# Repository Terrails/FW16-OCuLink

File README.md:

# OCuLink 8i Expansion Board for the Framework 16

## The schematic

The schematic in itself is pretty simple. You only need to connect the TX and RX PCIe lanes to the correct pins of the OCuLink connector. And then add components such as the EEPROM that the Embedded Controller (EC) on the laptop reads to configure GPIO pins and bifurcation.

A pdf version of the schematic is available [here](./imgs/schematic.pdf).

### EEPROM
As for the EEPROM, I have decided to use the same one that Framework is using in their [Dual SSD reference design](https://github.com/FrameworkComputer/ExpansionBay/tree/main/Dual%20SSD%20Reference%20Design). The `BR24G32FVT-3GE2`. The chip is marked as not recommended for new design according to Mouser, but it still seems to be in stock, although it can easily be swapped with another if required.

The EEPROM's address pins are all connected to the ground as that is the address the EC expects and by default the write protection (WP) is disabled by being connected to GND to allow writing data to it.

### Fans
For the fans I had to go with an alternative FPC header, as the one Framework uses on their boards was not available anywhere. The connector I use is slightly smaller, but still makes the connection nevertheless and the fans do spin up. I have specifically went with the [`AFC05-S04FIA-00`](https://www.lcsc.com/product-detail/C561383.html) that is available on LCSC to use with JLCPCB's assembly.

## Firmware
The firmware file is generated using [Framework's Expansion Bay tool](https://github.com/FrameworkComputer/ExpansionBayConfigurationGenerator). More info on the specific file I have been using in my testing and how I flashed it *SOON*.

## The PCB layout

For the layout I have went with a 4-layer board and did manage to successfully stay within JLCPCB's fabrication limits. For the production runs I have done a 1.2mm ENIG board and used the `Nan Ya NP-140F` material type with the `JLC04121H-1080` stackup and matched the differential pairs to it. I did also manage to stay within the minimum 0.3mm via hole size to keep costs somewhat down.

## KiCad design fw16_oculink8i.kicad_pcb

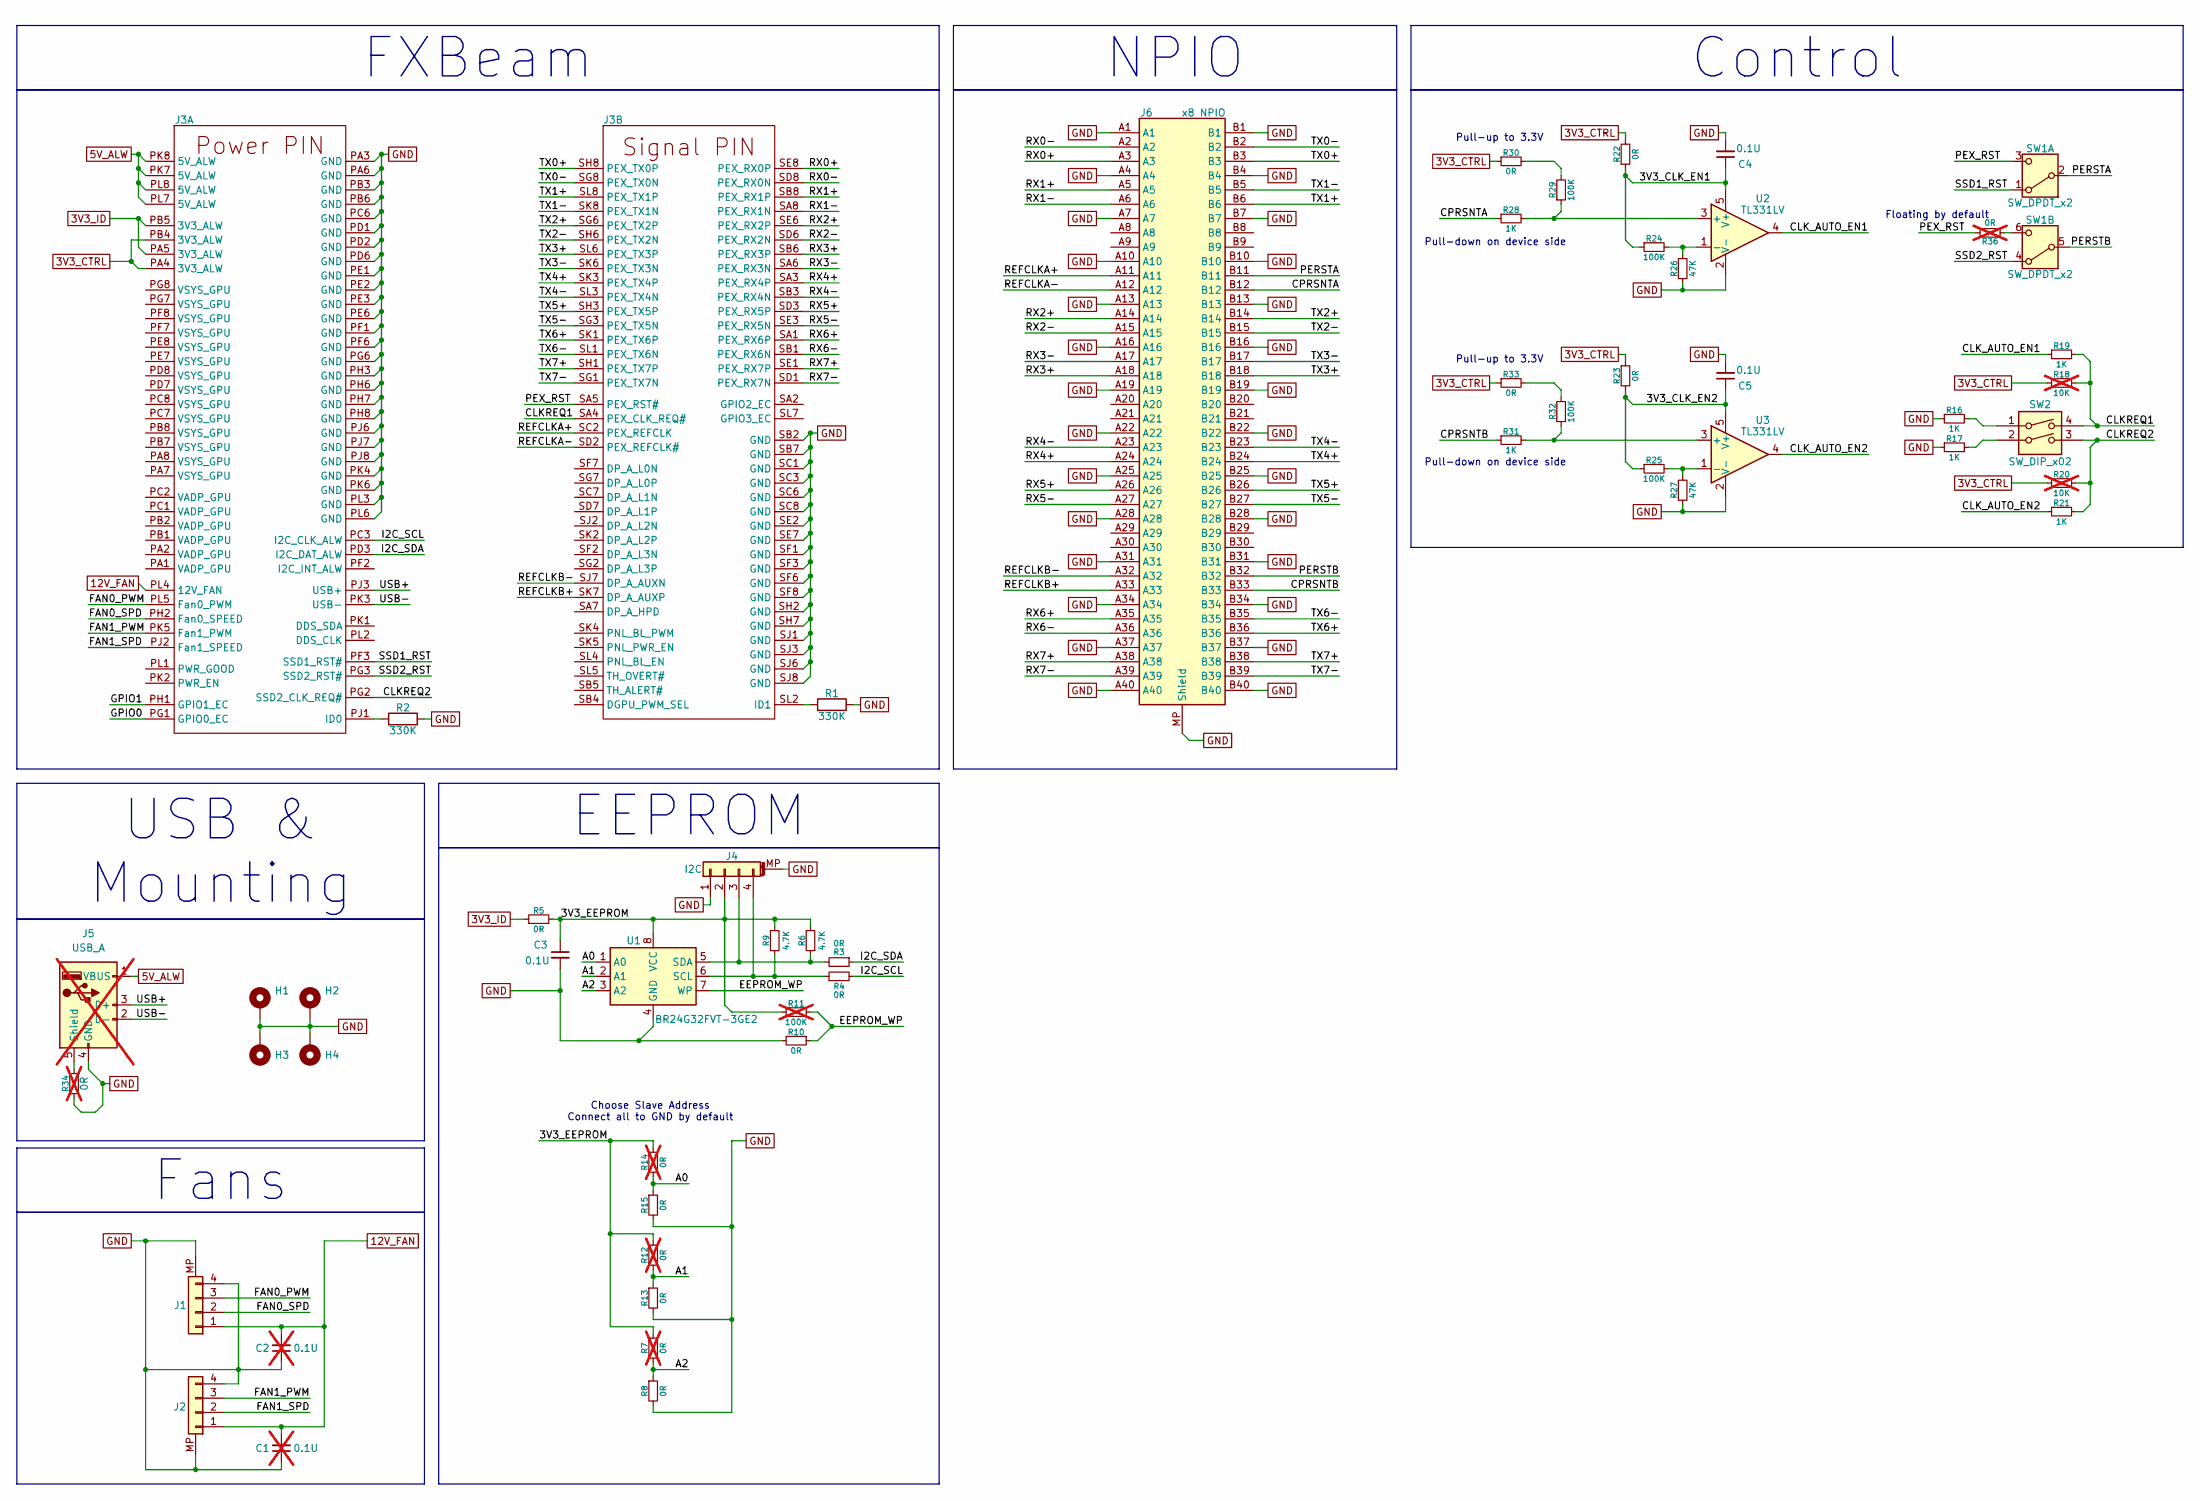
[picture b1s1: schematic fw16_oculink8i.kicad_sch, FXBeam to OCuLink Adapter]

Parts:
C1, C2: 0.1U; C_0402_1005Metric; not fitted
C3, C4, C5: 0.1U; C_0402_1005Metric
H1, H2, H3, H4: MountingHole_Pad; MountingHole_6.2mm_EasySolder_Cut
J1, J2: Fan; AFC58-S04FIA_4Pin; Part Nr. AFC58-S04FIA
J3: FXBeam
J4: I2C; JST_SH_SM04B-SRSS-TB_1x04-1MP_P1.00mm_Horizontal
J5: USB_A; 87583-2010BLF; not fitted
J6: x8 NPIO; Nano-Pitch-173162-0132
R1, R2: 330K; R_0402_1005Metric; Tolerance 1%
R3, R4, R5, R8, R10, R13, R15, R22, R23, R30, R33: 0R; R_0402_1005Metric
R6, R9: 4.7K; R_0402_1005Metric; Tolerance 1%
R7, R12, R14, R34, R36: 0R; R_0402_1005Metric; not fitted
R11: 100K; R_0402_1005Metric; Tolerance 1%; not fitted
R16, R17, R19, R21, R28, R31: 1K; R_0402_1005Metric
R18, R20: 10K; R_0402_1005Metric; not fitted
R24, R25, R29, R32: 100K; R_0402_1005Metric
R26, R27: 47K; R_0402_1005Metric
SW1: SW_DPDT_x2; SSSS820101
SW2: SW_DIP_x02; SW_DIP_SPSTx02_Slide_Copal_CHS-02B_W7.62mm_P1.27mm
U1: BR24G32FVT-3GE2; TSSOP-8_4.4x3mm_P0.65mm
U2, U3: TL331LV; SOT-23-5

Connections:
3V3_CTRL: J3.PA4 (3V3_ALW), J3.PB4 (3V3_ALW), R18.1, R20.1, R22.2, R23.1, R30.1, R33.1
3V3_ID: J3.PA5 (3V3_ALW), J3.PB5 (3V3_ALW), R5.1
5V_ALW: J3.PK7 (5V_ALW), J3.PK8 (5V_ALW), J3.PL7 (5V_ALW), J3.PL8 (5V_ALW), J5.1 (VBUS)
12V_FAN: C1.2, C2.2, J1.1, J2.1, J3.PL4 (12V_FAN)
/3V3_CLK_EN1: C4.1, R22.1, R24.1, U2.5 (V+)
/3V3_CLK_EN2: C5.1, R23.2, R25.1, U3.5 (V+)
/3V3_EEPROM: C3.1, J4.2, R5.2, R6.2, R7.1, R9.1, R11.2, R12.1, R14.1, U1.8 (VCC)
/A0: R14.2, R15.1, U1.1 (A0)
/A1: R12.2, R13.1, U1.2 (A1)
/A2: R7.2, R8.1, U1.3 (A2)
/CLKREQ1: J3.SA4 (PEX_CLK_REQ#), R18.2, R19.2, SW2.4
/CLKREQ2: J3.PG2 (SSD2_CLK_REQ#), R20.2, R21.2, SW2.3
/CLK_AUTO_EN1: R19.1, U2.4
/CLK_AUTO_EN2: R21.1, U3.4
/CPRSNTA: J6.B12, R28.1
/CPRSNTB: J6.B33, R31.1
/EEPROM_WP: R10.1, R11.1, U1.7 (WP)
/FAN0_PWM: J1.3, J3.PL5 (Fan0_PWM)
/FAN0_SPD: J1.2, J3.PH2 (Fan0_SPEED)
/FAN1_PWM: J2.3, J3.PK5 (Fan1_PWM)
/FAN1_SPD: J2.2, J3.PJ2 (Fan1_SPEED)
/GPIO0: J3.PG1 (GPIO0_EC)
/GPIO1: J3.PH1 (GPIO1_EC)
/I2C_SCL: J3.PC3 (I2C_CLK_ALW), R4.2
/I2C_SDA: J3.PD3 (I2C_DAT_ALW), R3.1
/PERSTA: J6.B11, SW1.2 (B)
/PERSTB: J6.B32, SW1.5 (B)
/PEX_RST: J3.SA5 (PEX_RST#), R36.2, SW1.3 (C)
/REFCLKA+: J3.SC2 (PEX_REFCLK), J6.A11
/REFCLKA-: J3.SD2 (PEX_REFCLK#), J6.A12
/REFCLKB+: J3.SK7 (DP_A_AUXP), J6.A33
/REFCLKB-: J3.SJ7 (DP_A_AUXN), J6.A32
/RX0+: J3.SE8 (PEX_RX0P), J6.A3
/RX0-: J3.SD8 (PEX_RX0N), J6.A2
/RX1+: J3.SB8 (PEX_RX1P), J6.A5
/RX1-: J3.SA8 (PEX_RX1N), J6.A6
/RX2+: J3.SE6 (PEX_RX2P), J6.A14
/RX2-: J3.SD6 (PEX_RX2N), J6.A15
/RX3+: J3.SB6 (PEX_RX3P), J6.A18
/RX3-: J3.SA6 (PEX_RX3N), J6.A17
/RX4+: J3.SA3 (PEX_RX4P), J6.A24
/RX4-: J3.SB3 (PEX_RX4N), J6.A23
/RX5+: J3.SD3 (PEX_RX5P), J6.A26
/RX5-: J3.SE3 (PEX_RX5N), J6.A27
/RX6+: J3.SA1 (PEX_RX6P), J6.A35
/RX6-: J3.SB1 (PEX_RX6N), J6.A36
/RX7+: J3.SE1 (PEX_RX7P), J6.A38
/RX7-: J3.SD1 (PEX_RX7N), J6.A39
/SSD1_RST: J3.PF3 (SSD1_RST#), SW1.1 (A)
/SSD2_RST: J3.PG3 (SSD2_RST#), SW1.4 (A)
/TX0+: J3.SH8 (PEX_TX0P), J6.B3
/TX0-: J3.SG8 (PEX_TX0N), J6.B2
/TX1+: J3.SL8 (PEX_TX1P), J6.B6
/TX1-: J3.SK8 (PEX_TX1N), J6.B5
/TX2+: J3.SG6 (PEX_TX2P), J6.B14
/TX2-: J3.SH6 (PEX_TX2N), J6.B15
/TX3+: J3.SL6 (PEX_TX3P), J6.B18
/TX3-: J3.SK6 (PEX_TX3N), J6.B17
/TX4+: J3.SK3 (PEX_TX4P), J6.B24
/TX4-: J3.SL3 (PEX_TX4N), J6.B23
/TX5+: J3.SH3 (PEX_TX5P), J6.B26
/TX5-: J3.SG3 (PEX_TX5N), J6.B27
/TX6+: J3.SK1 (PEX_TX6P), J6.B36
/TX6-: J3.SL1 (PEX_TX6N), J6.B35
/TX7+: J3.SH1 (PEX_TX7P), J6.B38
/TX7-: J3.SG1 (PEX_TX7N), J6.B39
/USB+: J3.PJ3 (USB+), J5.3 (D+)
/USB-: J3.PK3 (USB-), J5.2 (D-)
GND: C1.1, C2.1, C3.2, C4.2, C5.2, H1.1, H2.1, H3.1, H4.1, J1.4, J1.MP, J2.4, J2.MP, J3.PA3 (GND), J3.PA6 (GND), J3.PB3 (GND), J3.PB6 (GND), J3.PC6 (GND), J3.PD1 (GND), J3.PD2 (GND), J3.PD6 (GND), J3.PE1 (GND), J3.PE2 (GND), J3.PE3 (GND), J3.PE6 (GND), J3.PF1 (GND), J3.PF6 (GND), J3.PG6 (GND), J3.PH3 (GND), J3.PH6 (GND), J3.PH7 (GND), J3.PH8 (GND), J3.PJ6 (GND), J3.PJ7 (GND), J3.PJ8 (GND), J3.PK4 (GND), J3.PK6 (GND), J3.PL3 (GND), J3.PL6 (GND), J3.SB2 (GND), J3.SB7 (GND), J3.SC1 (GND), J3.SC3 (GND), J3.SC6 (GND), J3.SC8 (GND), J3.SE2 (GND), J3.SE7 (GND), J3.SF1 (GND), J3.SF3 (GND), J3.SF6 (GND), J3.SF8 (GND), J3.SH2 (GND), J3.SH7 (GND), J3.SJ1 (GND), J3.SJ3 (GND), J3.SJ6 (GND), J3.SJ8 (GND), J4.1, J4.MP (MountPin), J5.4 (GND), J6.A1, J6.A4, J6.A7, J6.A10, J6.A13, J6.A16, J6.A19, J6.A22, J6.A25, J6.A28, J6.A31, J6.A34, J6.A37, J6.A40, J6.B1, J6.B4, J6.B7, J6.B10, J6.B13, J6.B16, J6.B19, J6.B22, J6.B25, J6.B28, J6.B31, J6.B34, J6.B37, J6.B40, J6.MP (Shield), R1.1, R2.1, R8.2, R10.2, R13.2, R15.2, R16.1, R17.1, R26.1, R27.1, R34.2, U1.4 (GND), U2.2 (V-), U3.2 (V-)
unnamed: J3.PJ1 (ID0), R2.2
unnamed: J3.SL2 (ID1), R1.2
unnamed: J4.3, R3.2, R6.1, U1.5 (SDA)
unnamed: J4.4, R4.1, R9.2, U1.6 (SCL)
unnamed: J5.5 (Shield), R34.1
unnamed: R16.2, SW2.1
unnamed: R17.2, SW2.2
unnamed: R29.2, R30.2
unnamed: R32.2, R33.2
unnamed: R36.1, SW1.6 (C)
unnamed: R28.2, R29.1, U2.3 (+)
unnamed: R24.2, R26.2, U2.1 (-)
unnamed: R31.2, R32.1, U3.3 (+)
unnamed: R25.2, R27.2, U3.1 (-)

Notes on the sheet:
Pull-down on device side
Pull-up to 3.3V
Choose Slave Address Connect all to GND by default
Floating by default
Pull-down on device side
EEPROM
Fans
NPIO
FXBeam
USB & Mounting
Control

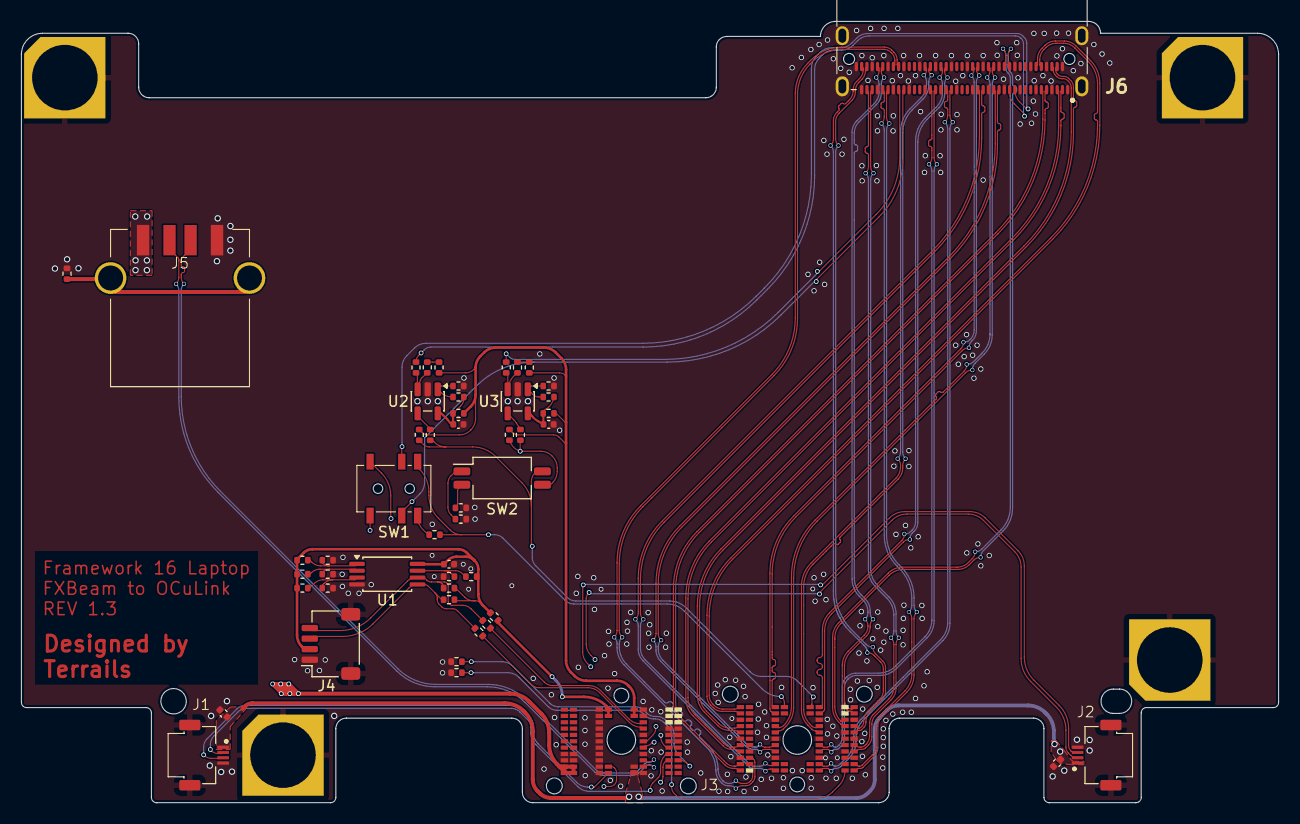
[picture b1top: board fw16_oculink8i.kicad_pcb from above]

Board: 4 copper layers, 119.0 x 73.9 mm, 55 parts (0 on the bottom side), 81 nets.

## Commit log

2025-08-28 resize page to a3 and add 3d model to nano-pitch connector
2025-08-28 improve: remove unnecessary circles and cleanup DRC
2025-08-28 Add 6-layer project
2025-08-28 Switch to 0R resistor rather than jumper solder pads
2025-08-28 Change resistor numbering
2025-08-28 schematic cleanup
2025-08-28 Add datasheets to parts
2025-08-28 Remove FXBeam from BOM
2025-08-28 Add R0 resistors to EEPROM power supply
2025-08-28 Configure board physical stackup
2025-08-28 Configure board finish to ENIG
2025-08-29 Add R0 resistor to CPRSNT oculink pin
2025-09-13 Remove unnecessary resistors from BOM
2025-09-15 Create separate nano-pitch footprint with JLC DRC rules
2025-09-15 Remove unnecessary vias
2025-11-15 Add CLKREQ trace and GND EEPROM WP resistor
2025-11-15 Update to rev 1.1 due to CLKREQ and EEPROM WP updates
2025-11-15 Update fill zones
2025-11-15 Add docs
2025-11-15 Add pdf location
2025-11-15 Update pcb image with new rev
2025-11-16 Finalize rev 1.1
2025-11-16 Fix pair skews
2025-11-16 Final cleanup
2025-11-23 update schematic and pcb imgs
2025-11-23 update board production details
2025-12-28 working rev1.1
2025-12-28 update images
2026-01-20 add IO-Shield step file
2026-01-23 Add MIT License to the project
2026-02-04 finalized rev1.2 order
2026-02-22 finalize rev1.3
2026-02-25 finalize rev1.3 for real now... maybe
